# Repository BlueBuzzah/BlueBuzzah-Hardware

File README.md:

# BlueBuzzah Hardware

Hardware design files for BlueBuzzah v3, an open-source research platform for
vibrotactile Coordinated Reset (vCR) stimulation, inspired by published research
in Parkinson's disease. This repository contains the files needed to manufacture the
physical components: PCB fabrication files, the board 3D model, and links to the
full build documentation.

## Overview

BlueBuzzah consists of two synchronized haptic gloves that deliver precisely
timed vibration patterns to the fingertips. Each glove requires:

- **Custom PCB** built around the ESP32-S3-WROOM-1U-N8R8 module (MCU + BLE), with
  five DRV2605L haptic drivers, a TCA9548A I2C multiplexer, an LSM6DS3 IMU, a
  WS2812B status LED, and five LRA motors (index, middle, ring, pinky, thumb)
- **Firmware** from the [BlueBuzzah-Firmware](https://github.com/BlueBuzzah/BlueBuzzah-Firmware) repository
- **Enclosure** — the v3 wearable enclosure has not been designed yet; see the
  wiki's Build Status page for the current state of the build

The board arrives fully assembled from JLCPCB's SMT service, and the tactor's
wire-to-LRA connection is a friction fit made by a 3D-printed wire plug — there
is no soldering anywhere in the build.

## Important notices

BlueBuzzah devices are not FDA cleared or approved medical devices and not intended to diagnose, treat, cure, mitigate, or prevent any disease. The information provided through BlueBuzzah is for general wellness purposes only and not a substitute for professional medical advice, diagnosis, or treatment.

**Important:** People with implanted electrodes from deep brain stimulation (DBS), heart pacemakers, or other internal electronic devices should take special precautions around all electronic devices, including BlueBuzzah. Consult your physician before use.

Read the [safety page](https://bluebuzzah.com/docs/safety) and the [terms and safety](https://bluebuzzah.com/terms) page before you build or wear a pair.

## Repository Contents

| Folder | Description |
| --- | --- |
| **[PCB/v3/](PCB/v3/)** | KiCad sources and the scripts that build the Gerbers, BOM and pick-and-place (CPL) for the v3 board |
| **[models/](models/)** | CAD files for the board, tactor and case (`STEP/`), the `.3mf` print file, a `.stl` for each 3D-printed part (`STL/`), and the `.glb` models used for the build guide's images (`GLB/`) |
| **[scripts/](scripts/)** | Headless Blender scripts that render the build guide's images from those models; see its [README](scripts/README.md) |

## Getting Started

The complete, step-by-step build guide lives at
**[bluebuzzah.com/docs](https://bluebuzzah.com/docs/)** — start there before
ordering parts.

Each [release](https://github.com/BlueBuzzah/BlueBuzzah-Hardware/releases) includes
two zips: `BlueBuzzah-v3-PCB.zip` holds the built JLCPCB and PCBWay order files,
and `BlueBuzzah-v3-parts.zip` holds every 3D-printed part.

### Manufacturing the PCB

The [`PCB/v3/`](PCB/v3/) folder contains everything needed for fabrication and
assembly. The order files aren't kept in the repo; the scripts build them into
`PCB/v3/build/`:

- `make_jlcpcb.py` — builds the JLCPCB order files (Gerber zip, BOM, CPL) into `build/jlcpcb/`
- `ORDERING-JLCPCB.md` — step-by-step JLCPCB ordering notes
- `make_pcbway.py` — builds separate PCBWay order files for one board, not panelized, into `build/pcbway/`
- `ORDERING-PCBWay.md` — step-by-step PCBWay ordering notes
- `kicad/` — KiCad schematic and PCB source files
- `panel/` — the KiKit panel the order files are built from

Upload the Gerber zip, BOM, and CPL to JLCPCB's SMT assembly service to order the
board fully assembled. See the wiki's "Ordering the PCB" page for details.

## Related Repositories

- **[BlueBuzzah-Firmware](https://github.com/BlueBuzzah/BlueBuzzah-Firmware)** - Firmware for the BlueBuzzah gloves.
- **[BlueBuzzah-Updater](https://github.com/BlueBuzzah/BlueBuzzah-Updater)** - Desktop application for updating and configuring BlueBuzzah devices.
- **[BlueBuzzah-Gloves](https://github.com/PWPInnovator898/BlueBuzzah-Gloves)** - The original v2 design, for reference.

## License

Each part of this repository is under the license that fits it. Where two rows overlap, the more specific path wins.

| Path | License | File |
| --- | --- | --- |
| `PCB/v3/` (KiCad sources, panel, Gerbers, BOM, CPL, PCBWay package) | CERN-OHL-S v2 | [`LICENSE-CERN-OHL-S-2.0.txt`](LICENSE-CERN-OHL-S-2.0.txt) |
| `models/`, `README.md`, `PCB/v3/**/*.md`, `scripts/README.md` | CC BY-SA 4.0 | [`LICENSE-CC-BY-SA-4.0.txt`](LICENSE-CC-BY-SA-4.0.txt) |
| `scripts/`, `tools/`, `PCB/v3/make_*.py` | MIT | [`LICENSE`](LICENSE) |

These third-party files are not relicensed and keep their own licenses:

- `models/STEP/USB_C_Receptacle_HRO_TYPE-C-31-M-12.step`: CERN-OHL-P v2, from KiCad's RoyalBlue54L demo.
- `PCB/v3/kicad/3dmodels/ESP32-S3-WROOM-1U.step`: Espressif's vendor model.
- `PCB/v3/kicad/Libraries/` and the KiCad standard library parts the board uses: the KiCad library license (CC BY-SA 4.0 with KiCad's exception for designs made with them).
- `scripts/fonts/`: SIL Open Font License (OFL files alongside).
- The board exports (`PCB/v3/kicad/BlueBuzzah_v3.step`, `models/STEP/BlueBuzzah-v3-pcb-model.step`, `models/GLB/bluebuzzah-v3-pcb.glb`, `models/GLB/bluebuzzah-exploded.glb`) include the part models above, which keep their own licenses.

The BlueBuzzah and BuzzahBuddy names and logos are not covered by these licenses. See [Licenses and the BlueBuzzah name](https://bluebuzzah.com/terms#licenses).

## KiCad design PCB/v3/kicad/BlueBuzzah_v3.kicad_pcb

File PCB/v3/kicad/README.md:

# KiCad Source Files

The KiCad schematic and PCB design source for the BlueBuzzah v3 board. Open `BlueBuzzah_v3.kicad_pro` in KiCad 10.

## Contents

- `BlueBuzzah_v3.kicad_pro` - KiCad project file
- `BlueBuzzah_v3.kicad_sch` - top-level schematic, plus `MCU_Power.kicad_sch` (module, USB and power) and `Buzzer_Drivers.kicad_sch` (haptic drivers)
- `BlueBuzzah_v3.kicad_pcb` - PCB layout
- `BlueBuzzah_v3.step` - 3D model of the assembled board
- `3dmodels/` - 3D model for the ESP32-S3-WROOM-1U-N8R8
- `Libraries/` - the slide switch footprint, and the DRV2605L symbol and footprint
- `fp-lib-table`, `sym-lib-table` - KiCad library tables
- `BlueBuzzah_v3.kicad_dru` - custom DRC rules for the six part pairs in tight gaps: R67 with C45 and U20; C45 with U20 and Q1; and SW2 with R43 and R45

Everything else comes from KiCad's standard libraries. KiCad has no 3D model for the USB-C connector (J10), so it's missing from the 3D view and the STEP file. J10's footprint keeps local shell-pad changes, and U1's pads are narrowed to 0.30 mm so PCBWay can keep a solder mask dam between them. KiCad reports both as different from their library copies.

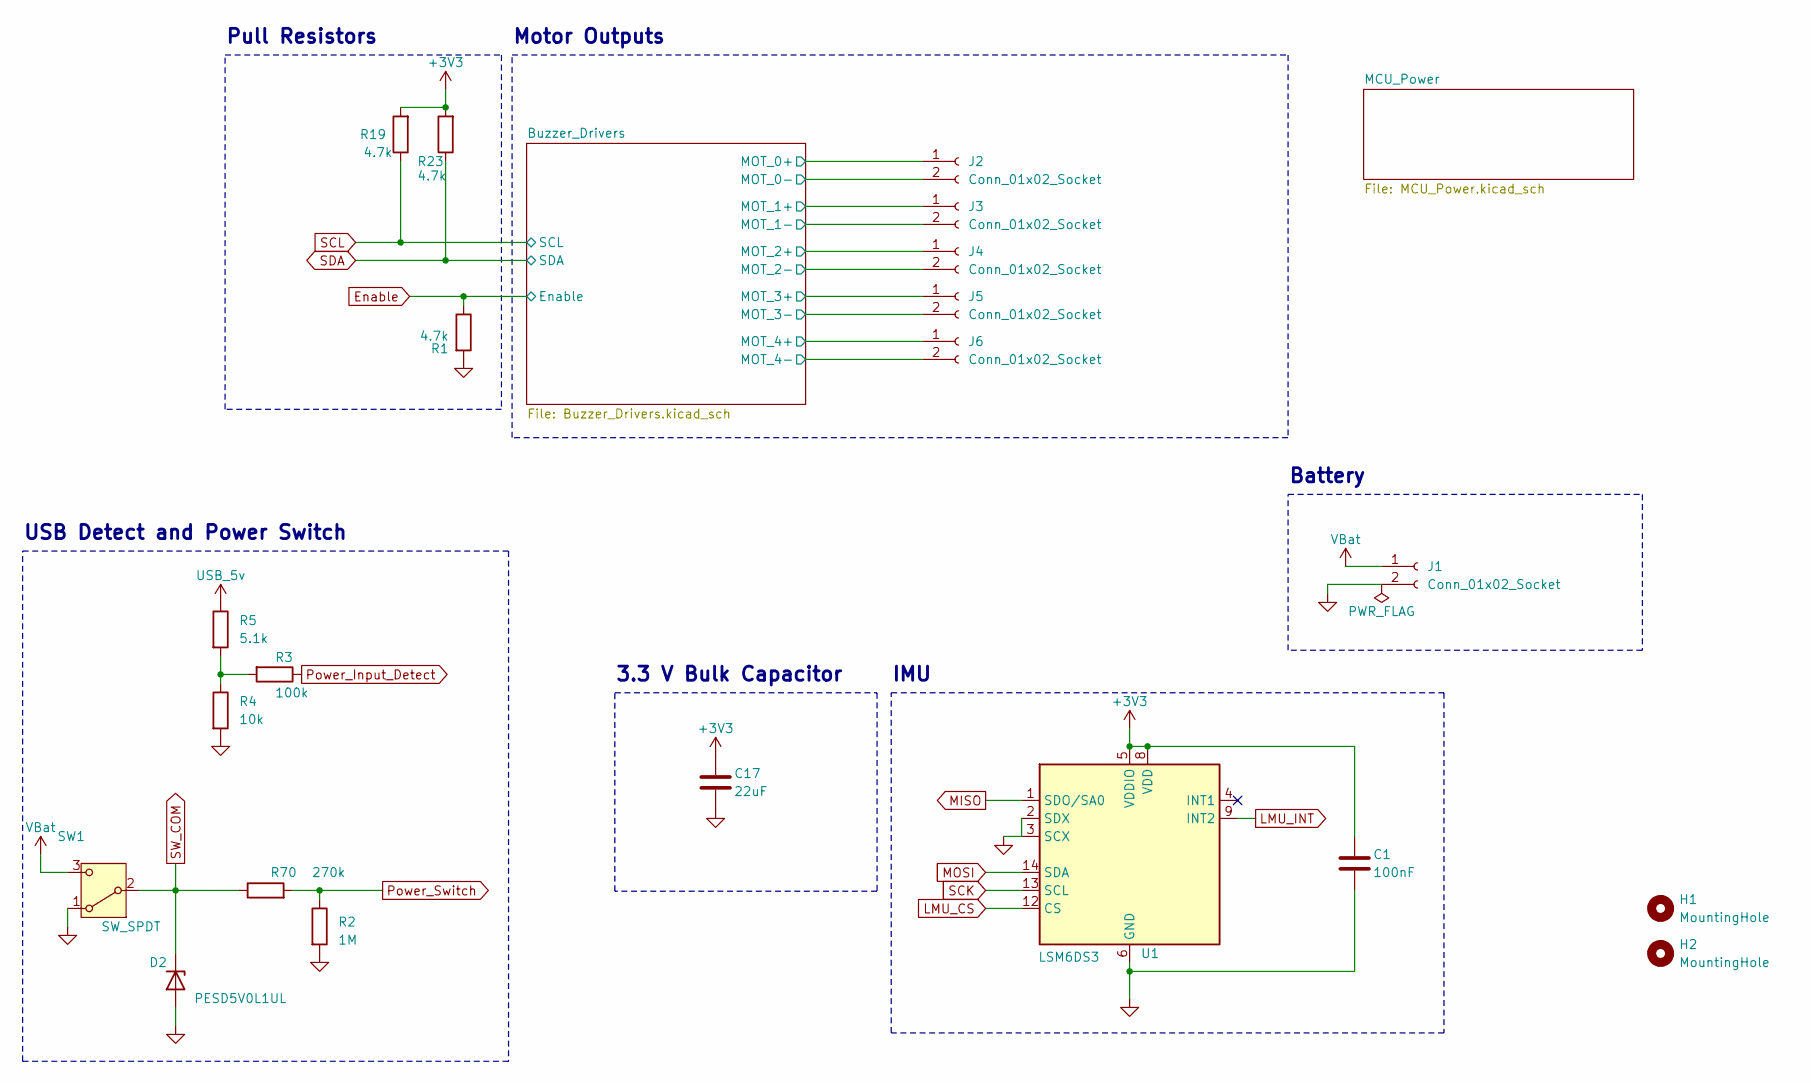
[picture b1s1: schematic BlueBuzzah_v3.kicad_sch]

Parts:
C1: 100nF; C_0402_1005Metric
C17: 22uF; C_1206_3216Metric
D2: PESD5V0L1UL; D_SOD-882
H1, H2: MountingHole; MountingHole_2.2mm_M2
J1, J2, J3, J4, J5, J6: Conn_01x02_Socket; JST_PH_S2B-PH-K_1x02_P2.00mm_Horizontal
R1, R19, R23: 4.7k; R_0402_1005Metric
R2: 1M; R_0402_1005Metric; LCSC C26083
R3: 100k; R_0402_1005Metric
R4: 10k; R_0402_1005Metric
R5: 5.1k; R_0402_1005Metric
R70: 270k; R_0402_1005Metric; LCSC C25770
SW1: SW_SPDT; SW_K3_1260D_L1_SPDT_Angled
U1: LSM6DS3; LGA-14_3x2.5mm_P0.5mm_LayoutBorder3x4y

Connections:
+3V3: C1.1, C17.1, R19.2, R23.2, U1.5 (VDDIO), U1.8 (VDD); also elsewhere on the board
/Buzzer_Drivers/MOT_0+: J2.1; also elsewhere on the board
/Buzzer_Drivers/MOT_0-: J2.2; also elsewhere on the board
/Buzzer_Drivers/MOT_1+: J3.1; also elsewhere on the board
/Buzzer_Drivers/MOT_1-: J3.2; also elsewhere on the board
/Buzzer_Drivers/MOT_2+: J4.1; also elsewhere on the board
/Buzzer_Drivers/MOT_2-: J4.2; also elsewhere on the board
/Buzzer_Drivers/MOT_3+: J5.1; also elsewhere on the board
/Buzzer_Drivers/MOT_3-: J5.2; also elsewhere on the board
/Buzzer_Drivers/MOT_4+: J6.1; also elsewhere on the board
/Buzzer_Drivers/MOT_4-: J6.2; also elsewhere on the board
Enable: R1.1; also elsewhere on the board
GND: C1.2, C17.2, D2.2 (A), J1.2, R1.2, R2.2, R4.2, SW1.1 (A), U1.2 (SDX), U1.3 (SCX), U1.6 (GND), U1.7 (GND); also elsewhere on the board
LMU_CS: U1.12 (CS); also elsewhere on the board
LMU_INT: U1.9 (INT2); also elsewhere on the board
MISO: U1.1 (SDO/SA0); also elsewhere on the board
MOSI: U1.14 (SDA); also elsewhere on the board
unnamed: R3.2, R4.1, R5.2
Power_Input_Detect: R3.1; also elsewhere on the board
Power_Switch: R2.1, R70.2; also elsewhere on the board
SCK: U1.13 (SCL); also elsewhere on the board
SCL: R19.1; also elsewhere on the board
SDA: R23.1; also elsewhere on the board
SW_COM: D2.1 (K), R70.1, SW1.2 (B); also elsewhere on the board
USB_5v: R5.1; also elsewhere on the board
VBat: J1.1, SW1.3 (C); also elsewhere on the board

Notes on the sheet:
Pull Resistors
Motor Outputs
USB Detect and Power Switch
Battery
3.3 V Bulk Capacitor
IMU

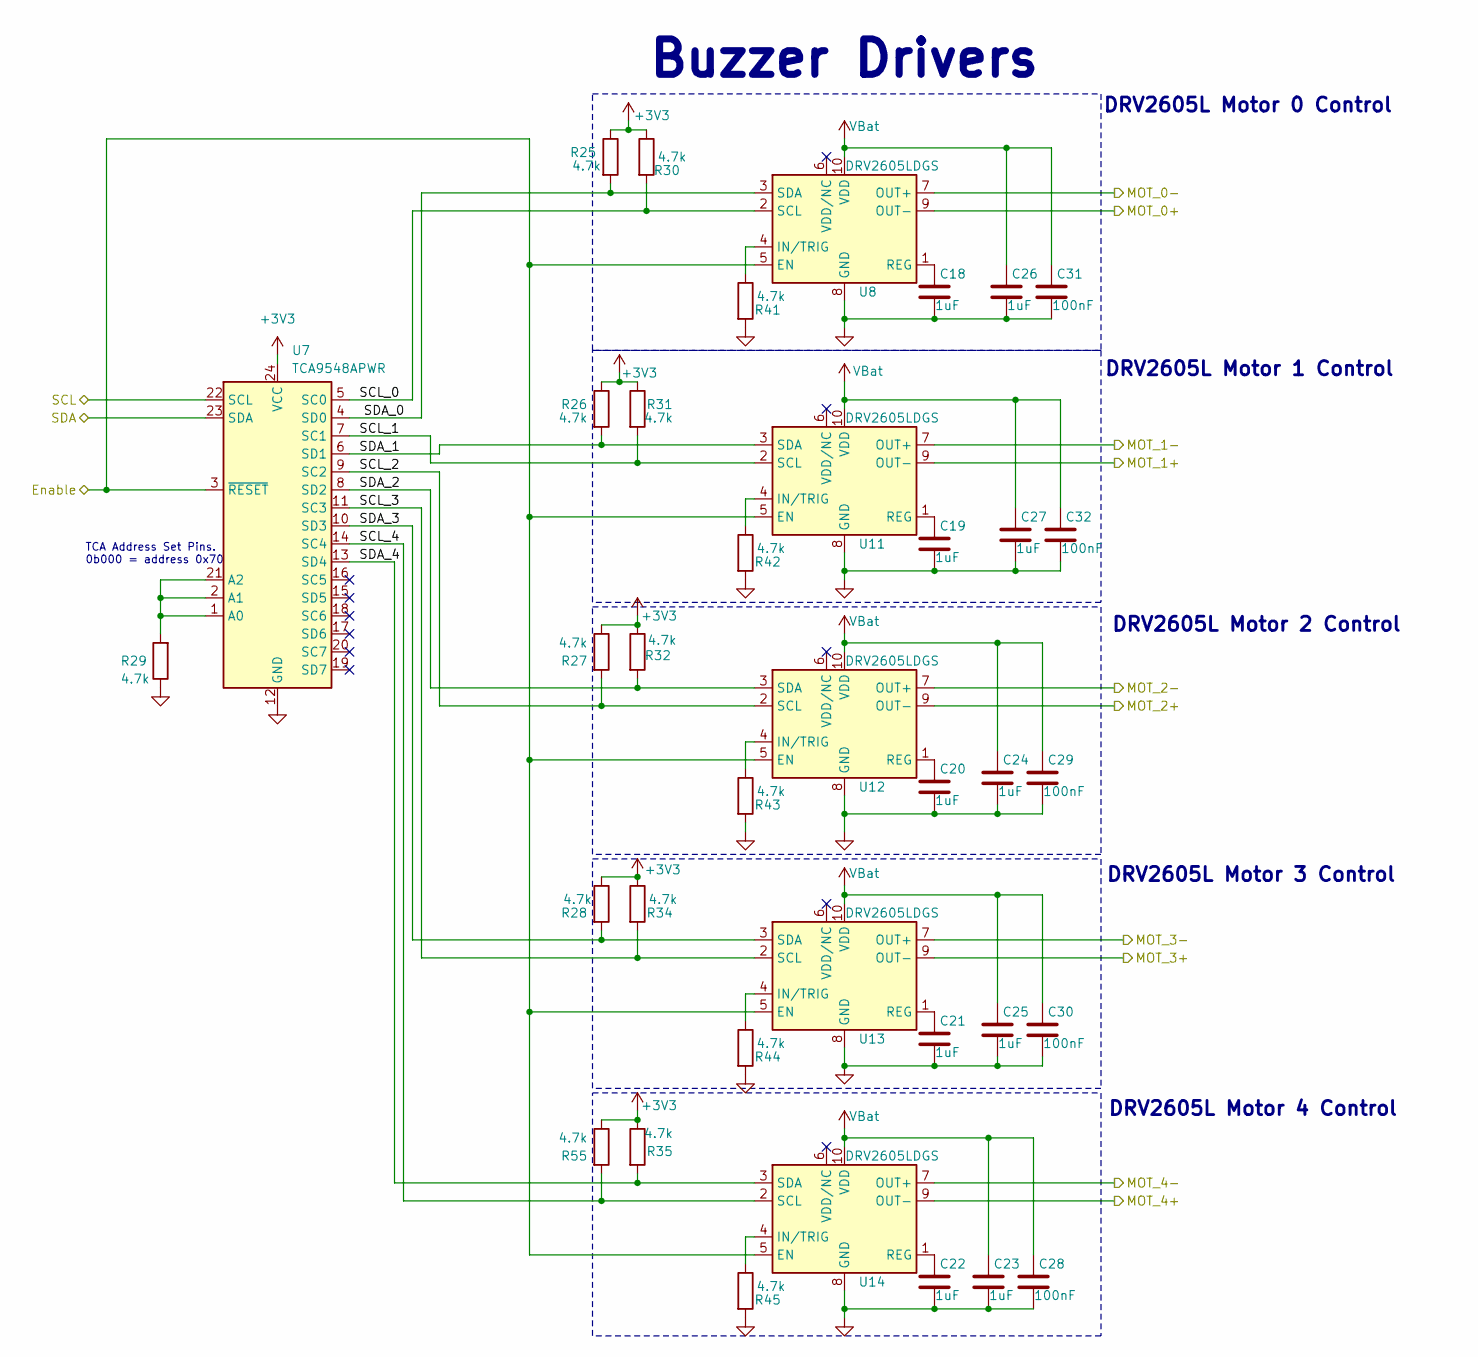
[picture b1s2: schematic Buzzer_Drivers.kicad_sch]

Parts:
C18, C19, C20, C21, C22, C23, C24, C25, C26, C27: 1uF; C_0402_1005Metric
C28, C29, C30, C31, C32: 100nF; C_0402_1005Metric
R25, R26, R27, R28, R29, R30, R31, R32, R34, R35, R41, R42, R43, R44, R45, R55: 4.7k; R_0402_1005Metric
U7: TCA9548APWR; TSSOP-24_4.4x7.8mm_P0.65mm
U8, U11, U12, U13, U14: DRV2605LDGS; VSSOP-10_3x3mm_P0.5mm

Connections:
+3V3: R25.1, R26.1, R27.1, R28.1, R30.1, R31.1, R32.1, R34.1, R35.1, R55.1, U7.24 (VCC); also elsewhere on the board
/Buzzer_Drivers/MOT_0+: U8.9 (OUT-); also elsewhere on the board
/Buzzer_Drivers/MOT_0-: U8.7 (OUT+); also elsewhere on the board
/Buzzer_Drivers/MOT_1+: U11.9 (OUT-); also elsewhere on the board
/Buzzer_Drivers/MOT_1-: U11.7 (OUT+); also elsewhere on the board
/Buzzer_Drivers/MOT_2+: U12.9 (OUT-); also elsewhere on the board
/Buzzer_Drivers/MOT_2-: U12.7 (OUT+); also elsewhere on the board
/Buzzer_Drivers/MOT_3+: U13.9 (OUT-); also elsewhere on the board
/Buzzer_Drivers/MOT_3-: U13.7 (OUT+); also elsewhere on the board
/Buzzer_Drivers/MOT_4+: U14.9 (OUT-); also elsewhere on the board
/Buzzer_Drivers/MOT_4-: U14.7 (OUT+); also elsewhere on the board
/Buzzer_Drivers/SCL_0: R30.2, U7.5 (SC0), U8.2 (SCL)
/Buzzer_Drivers/SCL_1: R31.2, U7.7 (SC1), U11.2 (SCL)
/Buzzer_Drivers/SCL_2: R27.2, U7.9 (SC2), U12.2 (SCL)
/Buzzer_Drivers/SCL_3: R34.2, U7.11 (SC3), U13.2 (SCL)
/Buzzer_Drivers/SCL_4: R55.2, U7.14 (SC4), U14.2 (SCL)
/Buzzer_Drivers/SDA_0: R25.2, U7.4 (SD0), U8.3 (SDA)
/Buzzer_Drivers/SDA_1: R26.2, U7.6 (SD1), U11.3 (SDA)
/Buzzer_Drivers/SDA_2: R32.2, U7.8 (SD2), U12.3 (SDA)
/Buzzer_Drivers/SDA_3: R28.2, U7.10 (SD3), U13.3 (SDA)
/Buzzer_Drivers/SDA_4: R35.2, U7.13 (SD4), U14.3 (SDA)
Enable: U7.3 (~RESET), U8.5 (EN), U11.5 (EN), U12.5 (EN), U13.5 (EN), U14.5 (EN); also elsewhere on the board
GND: C18.2, C19.2, C20.2, C21.2, C22.2, C23.2, C24.2, C25.2, C26.2, C27.2, C28.2, C29.2, C30.2, C31.2, C32.2, R29.1, R41.2, R42.2, R43.2, R44.2, R45.2, U7.12 (GND), U8.8 (GND), U11.8 (GND), U12.8 (GND), U13.8 (GND), U14.8 (GND); also elsewhere on the board
unnamed: R29.2, U7.1 (A0), U7.2 (A1), U7.21 (A2)
unnamed: R41.1, U8.4 (IN/TRIG)
unnamed: C18.1, U8.1 (REG)
unnamed: R42.1, U11.4 (IN/TRIG)
unnamed: C19.1, U11.1 (REG)
unnamed: R43.1, U12.4 (IN/TRIG)
unnamed: C20.1, U12.1 (REG)
unnamed: R44.1, U13.4 (IN/TRIG)
unnamed: C21.1, U13.1 (REG)
unnamed: R45.1, U14.4 (IN/TRIG)
unnamed: C22.1, U14.1 (REG)
SCL: U7.22 (SCL); also elsewhere on the board
SDA: U7.23 (SDA); also elsewhere on the board
VBat: C23.1, C24.1, C25.1, C26.1, C27.1, C28.1, C29.1, C30.1, C31.1, C32.1, U8.10 (VDD), U11.10 (VDD), U12.10 (VDD), U13.10 (VDD), U14.10 (VDD); also elsewhere on the board

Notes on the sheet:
DRV2605L Motor 2 Control
DRV2605L Motor 0 Control
TCA Address Set Pins. 0b000 = address 0x70
DRV2605L Motor 3 Control
DRV2605L Motor 4 Control
DRV2605L Motor 1 Control
Buzzer Drivers

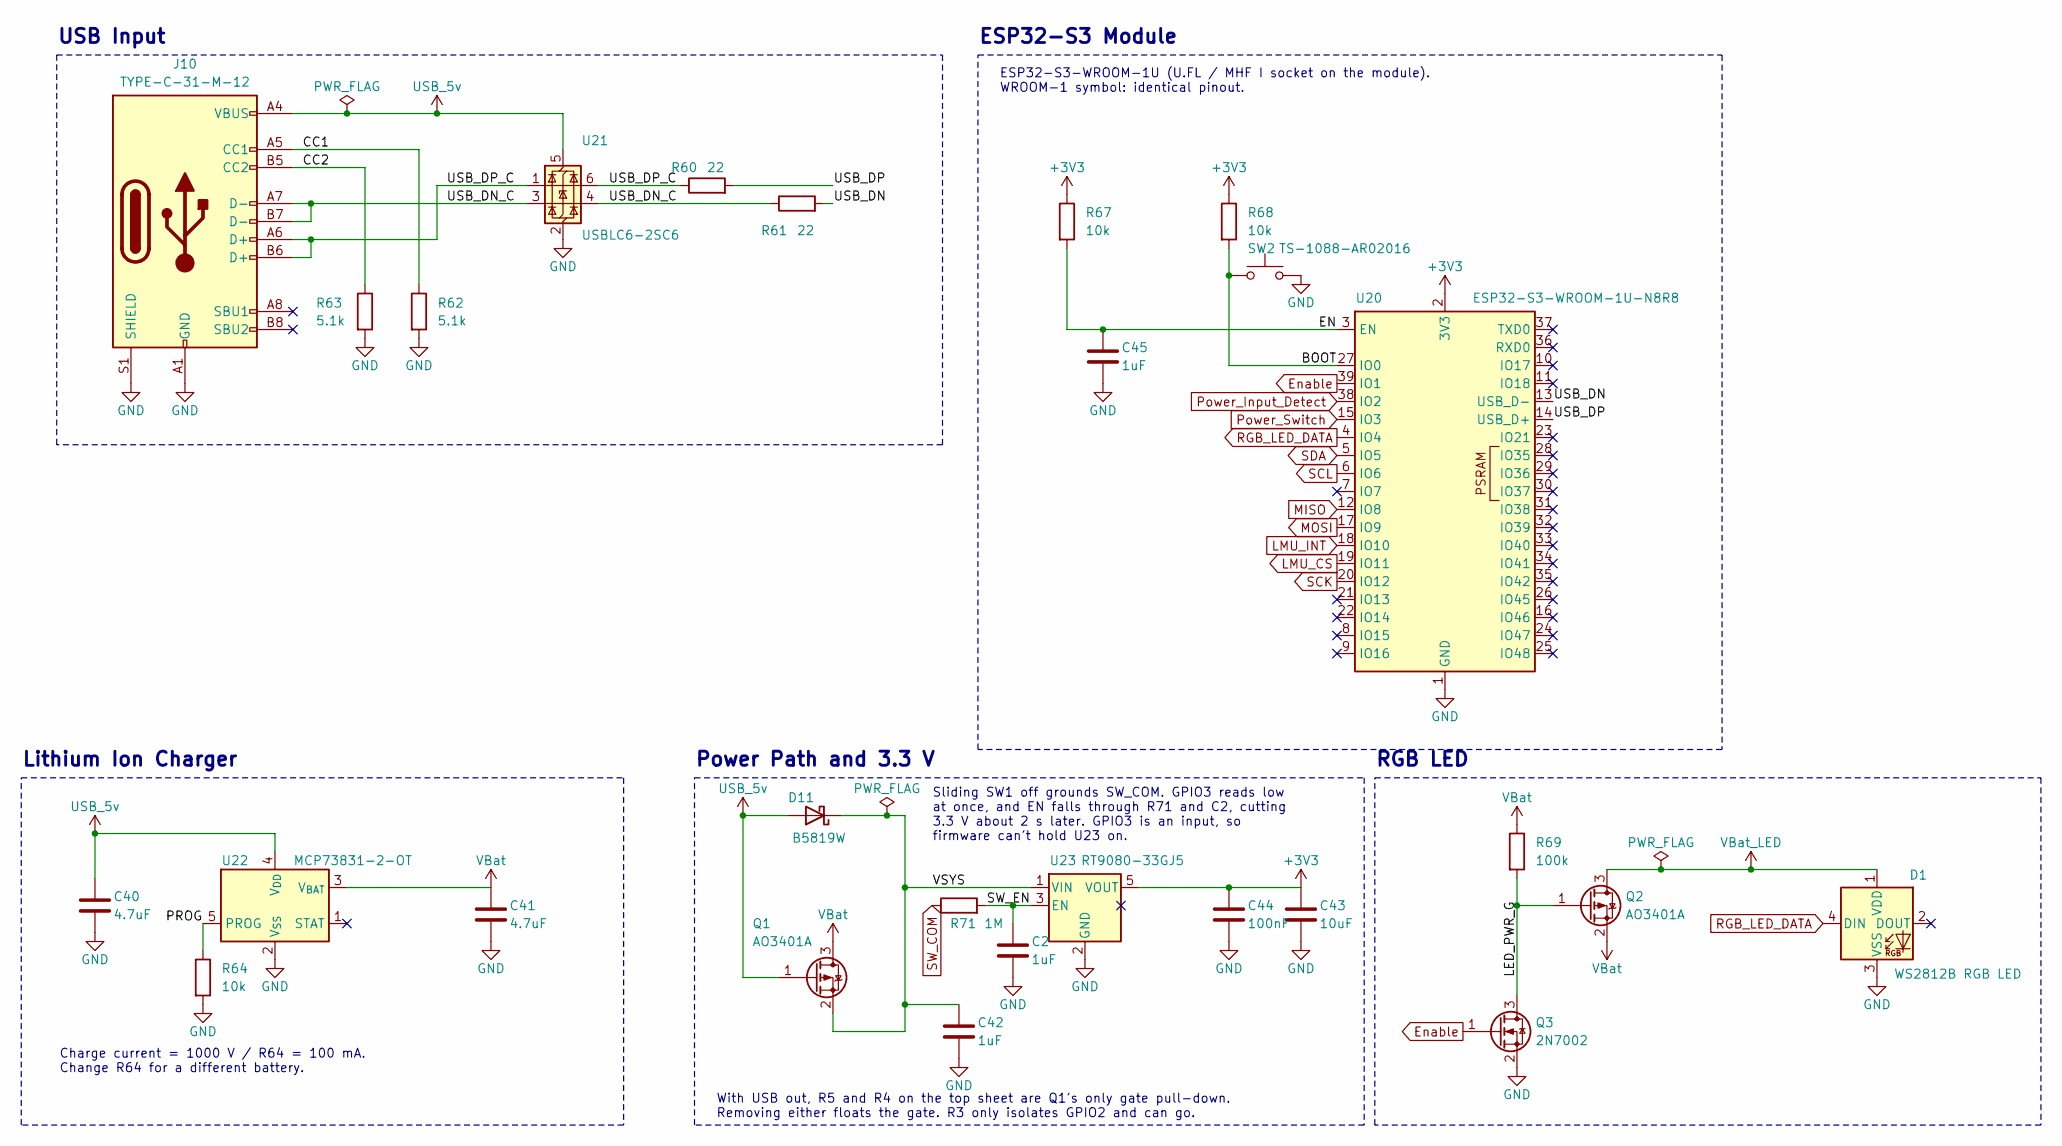
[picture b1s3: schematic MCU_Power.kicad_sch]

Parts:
C2, C42, C45: 1uF; C_0402_1005Metric; LCSC C52923
C40, C41: 4.7uF; C_0603_1608Metric; LCSC C19666
C43: 10uF; C_0402_1005Metric; LCSC C15525
C44: 100nF; C_0402_1005Metric; LCSC C1525
D1: WS2812B RGB LED; LED_WS2812B_PLCC4_5.0x5.0mm_P3.2mm
D11: B5819W; D_SOD-123; LCSC C8598
J10: TYPE-C-31-M-12; USB_C_Receptacle_HRO_TYPE-C-31-M-12; LCSC C165948
Q1, Q2: AO3401A; SOT-23; LCSC C15127
Q3: 2N7002; SOT-23; LCSC C8545
R60, R61: 22; R_0402_1005Metric; LCSC C25092
R62, R63: 5.1k; R_0402_1005Metric; LCSC C25905
R64, R67, R68: 10k; R_0402_1005Metric; LCSC C25744
R69: 100k; R_0402_1005Metric; LCSC C25741
R71: 1M; R_0402_1005Metric; LCSC C26083
SW2: TS-1088-AR02016; SW_SPST_TS-1088-xR020; LCSC C720477
U20: ESP32-S3-WROOM-1U-N8R8; ESP32-S3-WROOM-1U; LCSC C2980300
U21: USBLC6-2SC6; SOT-23-6; LCSC C7519
U22: MCP73831-2-OT; SOT-23-5; LCSC C424093
U23: RT9080-33GJ5; TSOT-23-5; LCSC C841192

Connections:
+3V3: C43.1, C44.1, R67.1, R68.1, U20.2 (3V3), U23.5 (VOUT); also elsewhere on the board
/MCU_Power/BOOT: R68.2, SW2.1, U20.27 (IO0)
/MCU_Power/CC1: J10.A5 (CC1), R62.1
/MCU_Power/CC2: J10.B5 (CC2), R63.1
/MCU_Power/EN: C45.1, R67.2, U20.3 (EN)
/MCU_Power/LED_PWR_G: Q2.1 (G), Q3.3 (D), R69.2
/MCU_Power/PROG: R64.1, U22.5 (PROG)
/MCU_Power/SW_EN: C2.1, R71.2, U23.3 (EN)
/MCU_Power/USB_DN: R61.2, U20.13 (USB_D-)
/MCU_Power/USB_DN_C: J10.A7 (D-), J10.B7 (D-), R61.1, U21.3 (I/O2), U21.4 (I/O2)
/MCU_Power/USB_DP: R60.2, U20.14 (USB_D+)
/MCU_Power/USB_DP_C: J10.A6 (D+), J10.B6 (D+), R60.1, U21.1 (I/O1), U21.6 (I/O1)
/MCU_Power/VSYS: C42.1, D11.1 (K), Q1.2 (S), U23.1 (VIN)
Enable: Q3.1 (G), U20.39 (IO1); also elsewhere on the board
GND: C2.2, C40.2, C41.2, C42.2, C43.2, C44.2, C45.2, D1.3 (VSS), J10.A1 (GND), J10.A12 (GND), J10.B1 (GND), J10.B12 (GND), J10.S1 (SHIELD), Q3.2 (S), R62.2, R63.2, R64.2, SW2.2, U20.1 (GND), U20.40 (GND), U20.41 (GND), U21.2 (GND), U22.2 (V_{SS}), U23.2 (GND); also elsewhere on the board
LMU_CS: U20.19 (IO11); also elsewhere on the board
LMU_INT: U20.18 (IO10); also elsewhere on the board
MISO: U20.12 (IO8); also elsewhere on the board
MOSI: U20.17 (IO9); also elsewhere on the board
Power_Input_Detect: U20.38 (IO2); also elsewhere on the board
Power_Switch: U20.15 (IO3); also elsewhere on the board
RGB_LED_DATA: D1.4 (DIN), U20.4 (IO4)
SCK: U20.20 (IO12); also elsewhere on the board
SCL: U20.6 (IO6); also elsewhere on the board
SDA: U20.5 (IO5); also elsewhere on the board
SW_COM: R71.1; also elsewhere on the board
USB_5v: C40.1, D11.2 (A), J10.A4 (VBUS), J10.A9 (VBUS), J10.B4 (VBUS), J10.B9 (VBUS), Q1.1 (G), U21.5 (VBUS), U22.4 (V_{DD}); also elsewhere on the board
VBat: C41.1, Q1.3 (D), Q2.2 (S), R69.1, U22.3 (V_{BAT}); also elsewhere on the board
VBat_LED: D1.1 (VDD), Q2.3 (D)

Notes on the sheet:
ESP32-S3-WROOM-1U (U.FL / MHF I socket on the module). WROOM-1 symbol: identical pinout.
Charge current = 1000 V / R64 = 100 mA. Change R64 for a different battery.
With USB out, R5 and R4 on the top sheet are Q1's only gate pull-down. Removing either floats the gate. R3 only isolates GPIO2 and can go.
Sliding SW1 off grounds SW_COM. GPIO3 reads low at once, and EN falls through R71 and C2, cutting 3.3 V about 2 s later. GPIO3 is an input, so firmware can't hold U23 on.
USB Input
ESP32-S3 Module
Lithium Ion Charger
Power Path and 3.3 V
RGB LED

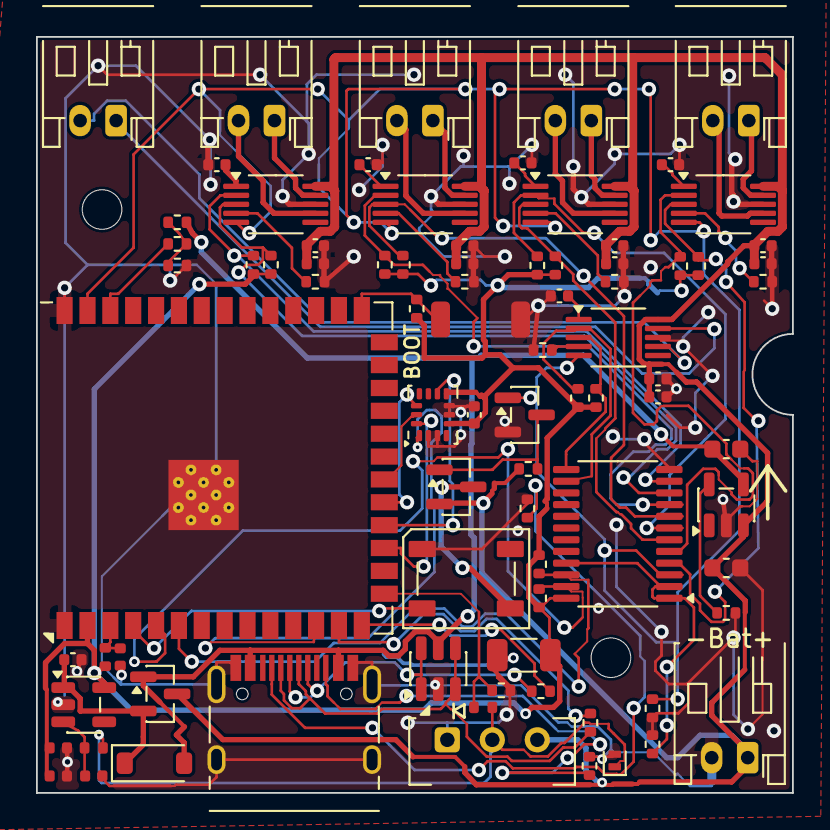
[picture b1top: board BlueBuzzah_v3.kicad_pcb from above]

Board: 2 copper layers, 42.0 x 42.0 mm, 85 parts (0 on the bottom side), 61 nets.

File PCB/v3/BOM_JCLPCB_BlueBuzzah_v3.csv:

Comment,Designator,Footprint,JLCPCB Part #
100nF,"C1_1,C28_1,C29_1,C30_1,C31_1,C32_1,C44_1",C_0402_1005Metric,C1525
1uF,"C2_1,C18_1,C19_1,C20_1,C21_1,C22_1,C23_1,C24_1,C25_1,C26_1,C27_1,C42_1,C45_1",C_0402_1005Metric,C52923
22uF,C17_1,C_1206_3216Metric,C12891
4.7uF,"C40_1,C41_1",C_0603_1608Metric,C19666
10uF,C43_1,C_0402_1005Metric,C15525
WS2812B RGB LED,D1_1,LED_WS2812B_PLCC4_5.0x5.0mm_P3.2mm,C2874885
PESD5V0L1UL,D2_1,D_SOD-882,C3001948
B5819W,D11_1,D_SOD-123,C8598
Conn_01x02_Socket,"J1_1,J2_1,J3_1,J4_1,J5_1,J6_1",JST_PH_S2B-PH-K_1x02_P2.00mm_Horizontal,C5175239
TYPE-C-31-M-12,J10_1,USB_C_Receptacle_HRO_TYPE-C-31-M-12,C165948
AO3401A,"Q1_1,Q2_1",SOT-23,C15127
2N7002,Q3_1,SOT-23,C8545
4.7k,"R1_1,R19_1,R23_1,R25_1,R26_1,R27_1,R28_1,R29_1,R30_1,R31_1,R32_1,R34_1,R35_1,R41_1,R42_1,R43_1,R44_1,R45_1,R55_1",R_0402_1005Metric,C25900
1M,"R2_1,R71_1",R_0402_1005Metric,C26083
100k,"R3_1,R69_1",R_0402_1005Metric,C25741
10k,"R4_1,R64_1,R67_1,R68_1",R_0402_1005Metric,C25744
5.1k,"R5_1,R62_1,R63_1",R_0402_1005Metric,C25905
22,"R60_1,R61_1",R_0402_1005Metric,C25092
270k,R70_1,R_0402_1005Metric,C25770
SW_SPDT,SW1_1,SW_K3_1260D_L1_SPDT_Angled,C92657
TS-1088-AR02016,SW2_1,SW_SPST_TS-1088-xR020,C720477
LSM6DS3,U1_1,LGA-14_3x2.5mm_P0.5mm_LayoutBorder3x4y,C967633
TCA9548APWR,U7_1,TSSOP-24_4.4x7.8mm_P0.65mm,C130026
DRV2605LDGS,"U8_1,U11_1,U12_1,U13_1,U14_1",VSSOP-10_3x3mm_P0.5mm,C527464
ESP32-S3-WROOM-1U-N8R8,U20_1,ESP32-S3-WROOM-1U,C2980300
USBLC6-2SC6,U21_1,SOT-23-6,C7519
MCP73831-2-OT,U22_1,SOT-23-5,C424093
RT9080-33GJ5,U23_1,TSOT-23-5,C841192

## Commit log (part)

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2025-12-06 Initial commit of existing resources and documentation

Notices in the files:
PCB/v3/kicad/BlueBuzzah_v3.kicad_pcb:
Copyright BlueBuzzah Partners. Licensed under CERN-OHL-S-2.0.
README.md:
License: MIT | CERN-OHL-S | CC BY-SA
